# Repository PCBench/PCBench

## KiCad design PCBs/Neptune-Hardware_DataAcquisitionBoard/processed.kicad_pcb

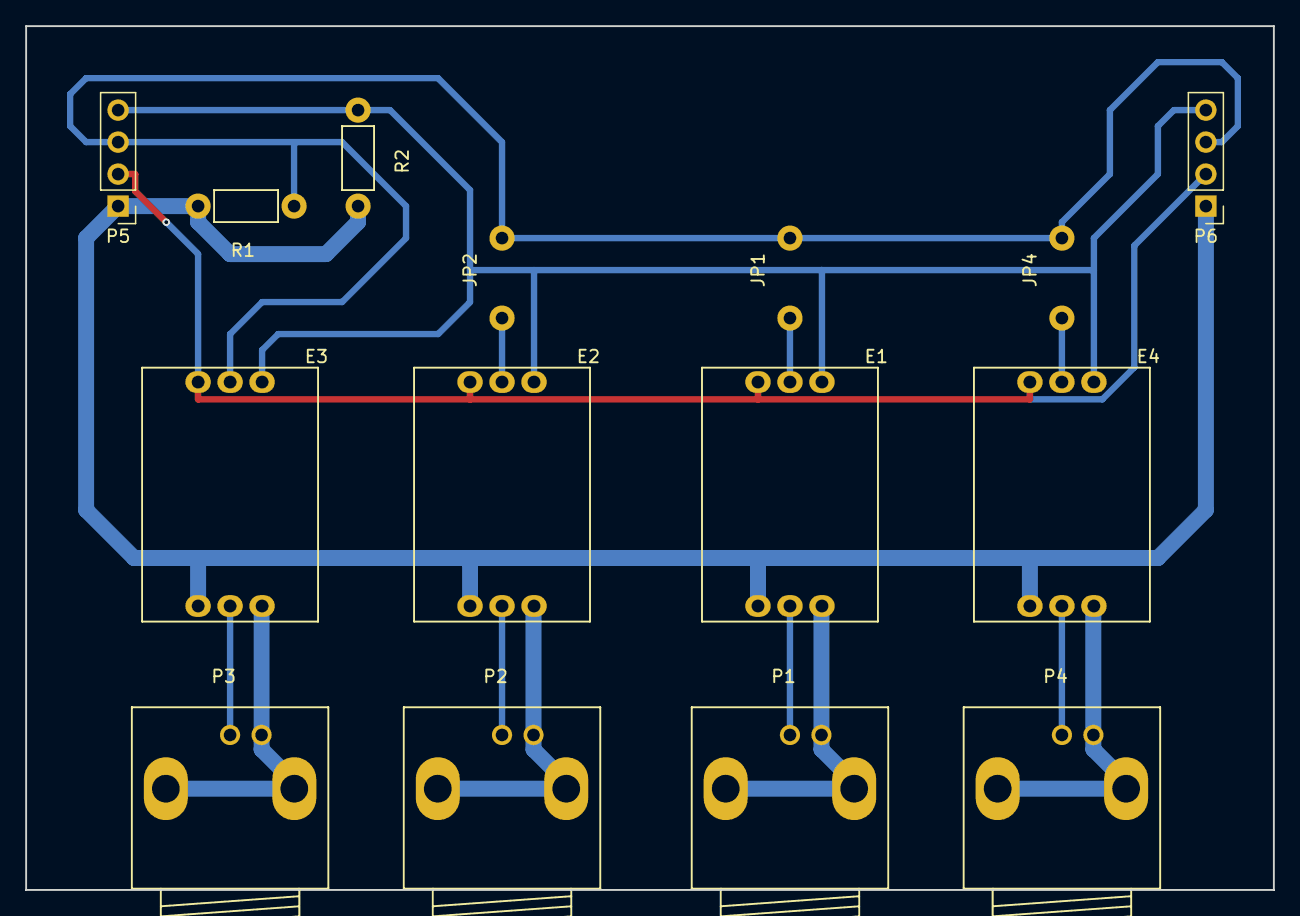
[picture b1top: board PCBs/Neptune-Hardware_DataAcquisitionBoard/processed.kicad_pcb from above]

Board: 2 copper layers, 99.1 x 68.6 mm, 15 parts (0 on the bottom side), 15 nets.

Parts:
E1, E3, E4: phEZO
E2: DO_EZO; phEZO
JP1, JP2, JP4: JUMPER; Jumper_6.35mm
P1, P2, P3, P4: BNC; BNC_Socket_TYCO-AMP
P5, P6: CONN_01X04; Pin_Header_Straight_1x04_Pitch2.54mm
R1, R2: 12K; Resistor_Horizontal_RM7mm

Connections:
+5V: E1.6, E2.6, E3.6, E4.6, P5.1, P6.1, R1.2, R2.2
A4: E3.2, JP1.2, JP2.2, JP4.2, P5.3, P6.3, R1.1
A5: E1.3, E2.3, E3.3, E4.3, P5.4, P6.4, R2.1
GND: E1.1, E2.1, E3.1, E4.1, P5.2, P6.2
unnamed: E1.2, JP1.1
unnamed: E1.4, P1.2
unnamed: E1.5, P1.1
unnamed: E2.2, JP2.1
unnamed: E2.4, P2.2
unnamed: E2.5, P2.1
unnamed: E3.4, P3.2
unnamed: E3.5, P3.1
unnamed: E4.2, JP4.1
unnamed: E4.4, P4.2
unnamed: E4.5, P4.1

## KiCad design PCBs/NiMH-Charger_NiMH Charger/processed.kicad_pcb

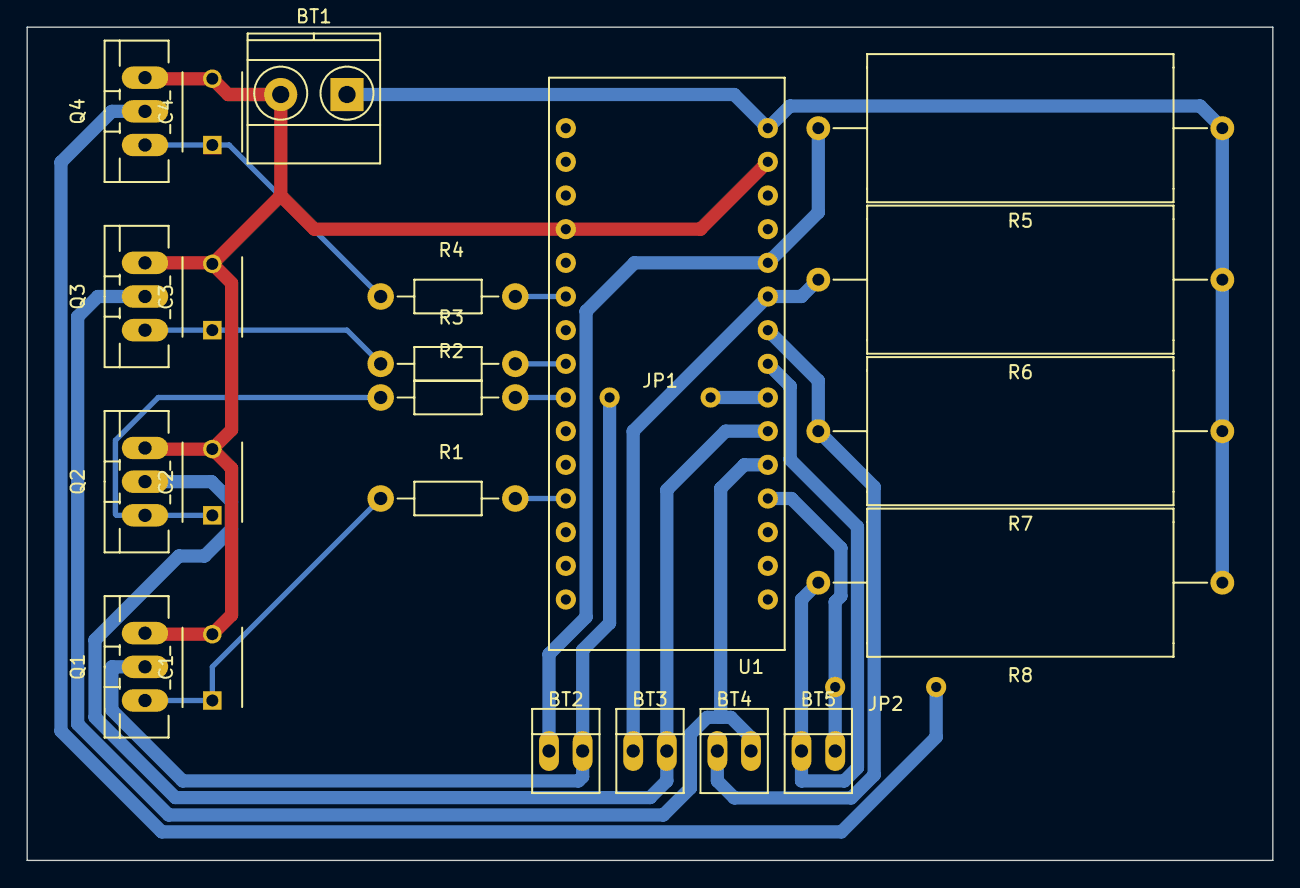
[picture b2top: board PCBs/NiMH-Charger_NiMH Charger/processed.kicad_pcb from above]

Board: 2 copper layers, 94.0 x 62.9 mm, 24 parts (0 on the bottom side), 20 nets.

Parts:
BT1: Battery; TerminalBlock_Pheonix_MKDS1.5-2pol
BT2, BT3, BT4, BT5: Battery; PINHEAD1-2
C1, C2, C3, C4: 1uF; C_Disc_D6_P5
JP1, JP2: JUMPER; Jumper
Q1, Q2, Q3, Q4: IRF510; TO-220_Neutral123_Vertical_LargePads
R1, R2, R3, R4: 10M; Resistor_Horizontal_RM10mm
R5, R6, R7, R8: 10R; Resistor_Ceramic_Horizontal_L23mm-W9mm-H9mm-p30mm
U1: Arduino_NANO

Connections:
/GND: BT1.2, C1.2, C2.2, C3.2, C4.2, Q1.3, Q2.3, Q3.3, Q4.3, U1.14, U1.19
/VIN: BT1.1, R5.1, R6.1, R7.1, R8.1, U1.15
unnamed: BT2.1, R5.2, U1.11
unnamed: BT2.2, JP1.2, Q1.2
unnamed: BT3.1, R6.2, U1.10
unnamed: BT3.2, Q2.2, U1.6
unnamed: BT4.1, R7.2, U1.9
unnamed: BT4.2, Q3.2, U1.5
unnamed: BT5.1, R8.2, U1.8
unnamed: BT5.2, JP2.1, U1.4
unnamed: C1.1, Q1.1, R1.1
unnamed: C2.1, Q2.1, R2.1
unnamed: C3.1, Q3.1, R3.1
unnamed: C4.1, Q4.1, R4.1
unnamed: JP1.1, U1.7
unnamed: JP2.2, Q4.2
unnamed: R1.2, U1.27
unnamed: R2.2, U1.24
unnamed: R3.2, U1.23
unnamed: R4.2, U1.21

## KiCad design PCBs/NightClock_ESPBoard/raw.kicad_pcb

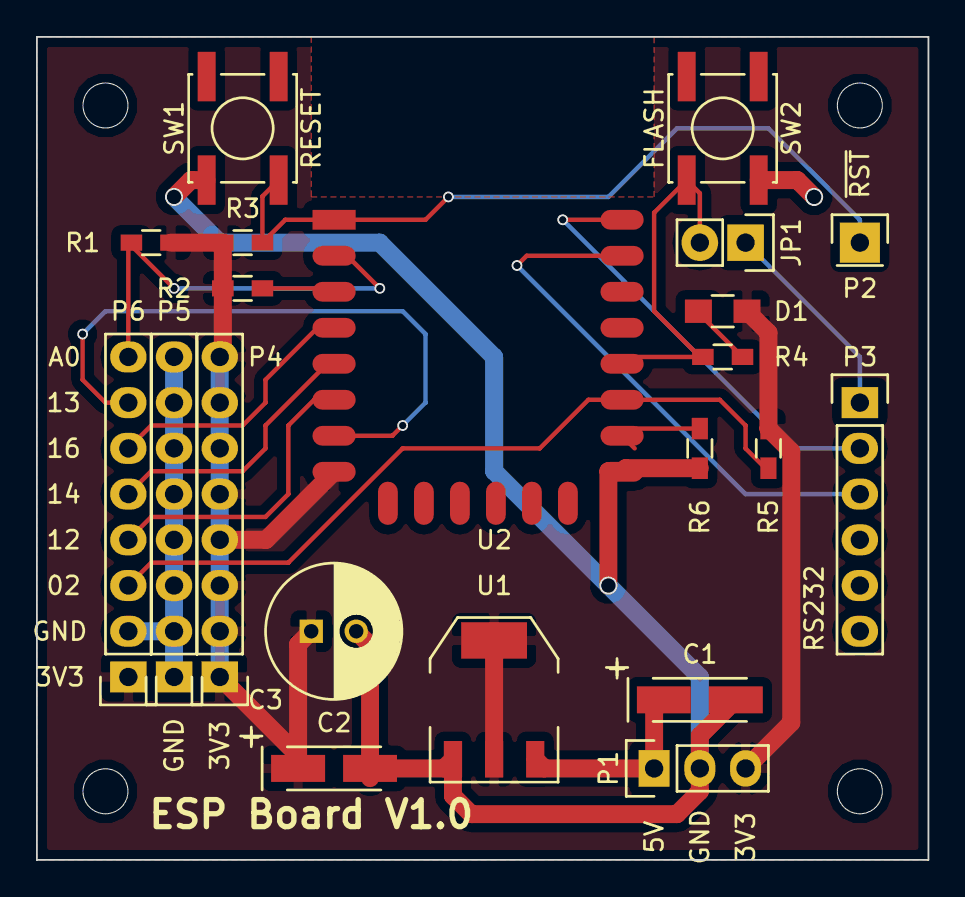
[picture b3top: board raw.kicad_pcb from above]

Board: 2 copper layers, 49.5 x 45.7 mm, 21 parts (0 on the bottom side), 17 nets.

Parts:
C1, C2: 10u; TantalC_SizeA_EIA-3216_HandSoldering
C3: 1000u; C_Radial_D7.5_L11.2_P2.5
D1: LED; R_0805_HandSoldering
JP1: AUTO_FLASH; Pin_Header_Straight_1x02
P1: PWR; Pin_Header_Straight_1x03
P2: EXT_RESET; Pin_Header_Straight_1x01
P3: RS232; Pin_Header_Straight_1x06
P4: 3.3V; Pin_Header_Straight_1x08
P5: Gnd; Pin_Header_Straight_1x08
P6: GPIO; Pin_Header_Straight_1x08
R1: 470k; R_0603_HandSoldering
R2, R3, R5, R6: 10k; R_0603_HandSoldering
R4: 330R; R_0603_HandSoldering
SW1: RESET; SW_SPST_EVPBF
SW2: FLASH; SW_SPST_EVPBF
U1: LM1117-3.3; SOT-223
U2: ESP-12E

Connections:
+3V3: C2.1, C3.1, D1.2, P1.3, P4.1, P4.2, P4.3, P4.4, P4.5, P4.6, P4.7, P4.8, P6.1, R1.1, R2.1, R3.1, R5.1, U1.2, U1.4, U2.8
+5V: C1.1, P1.1, U1.3
/ESP_ADC: P6.8, R1.2, U2.2
/ESP_CH_PD: R2.2, U2.3
/ESP_GPIO0: JP1.2, R4.2, SW2.2, U2.18
/ESP_GPIO2: P6.3, R5.2, U2.17
/ESP_GPIO12: P6.4, U2.6
/ESP_GPIO13: P6.7, U2.7
/ESP_GPIO14: P6.5, U2.5
/ESP_GPIO15: R6.1, U2.16
/ESP_GPIO16: P6.6, U2.4
/ESP_RESET: P2.1, R3.2, SW1.2, U2.1
/ESP_RX_IN: P3.3, U2.21
/ESP_TX_OUT: P3.2, U2.22
/SERIAL_DTR: JP1.1, P3.1
GNDPWR: C1.2, C2.2, C3.2, P1.2, P3.6, P5.1, P5.2, P5.3, P5.4, P5.5, P5.6, P5.7, P5.8, P6.2, R6.2, SW1.1, SW2.1, U1.1, U2.15
unnamed: D1.1, R4.1

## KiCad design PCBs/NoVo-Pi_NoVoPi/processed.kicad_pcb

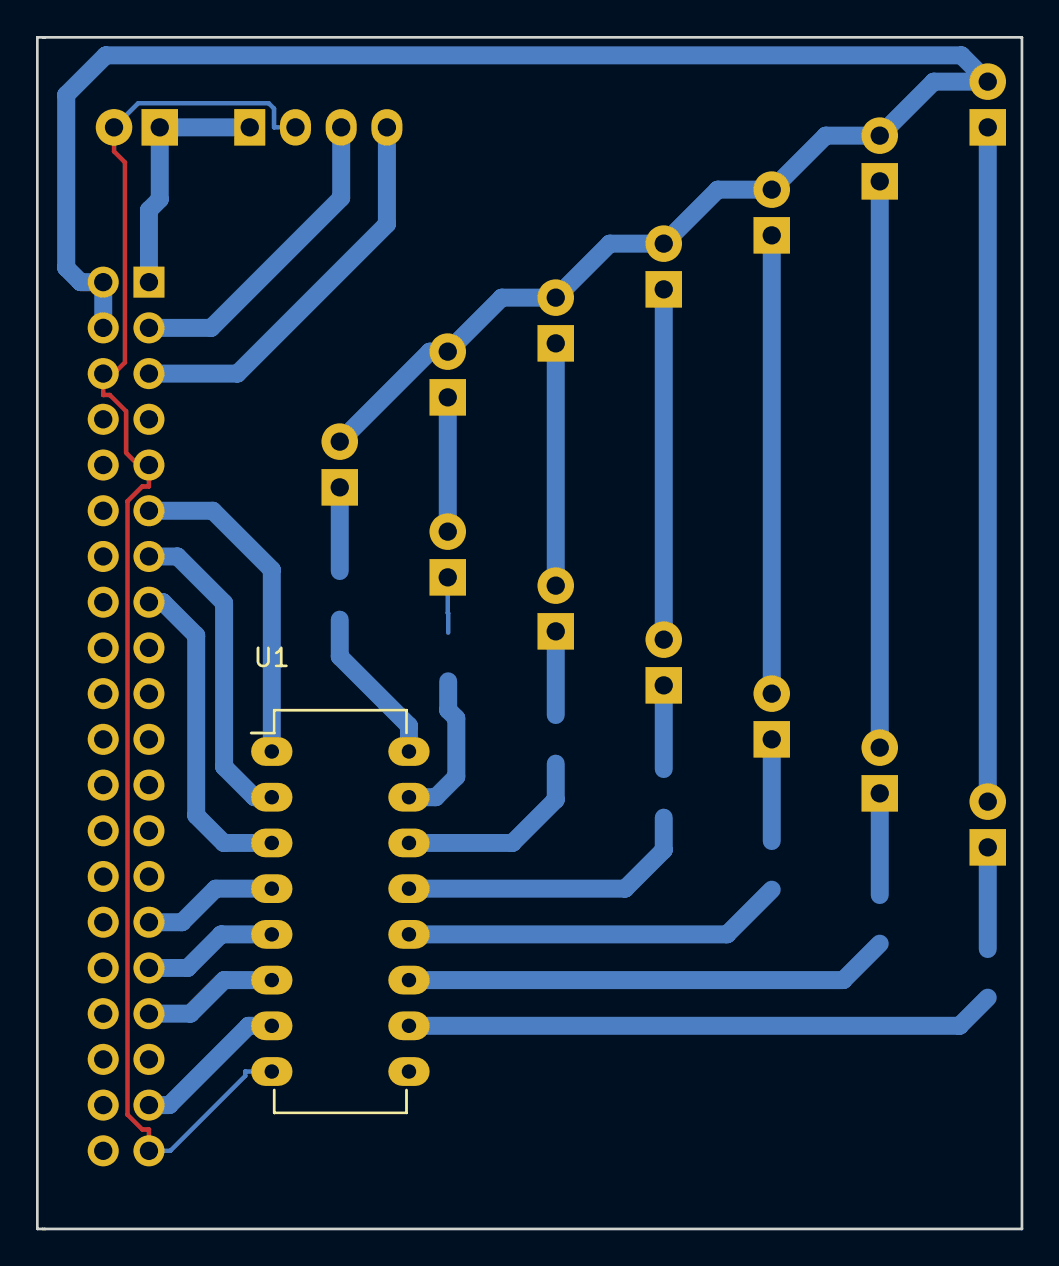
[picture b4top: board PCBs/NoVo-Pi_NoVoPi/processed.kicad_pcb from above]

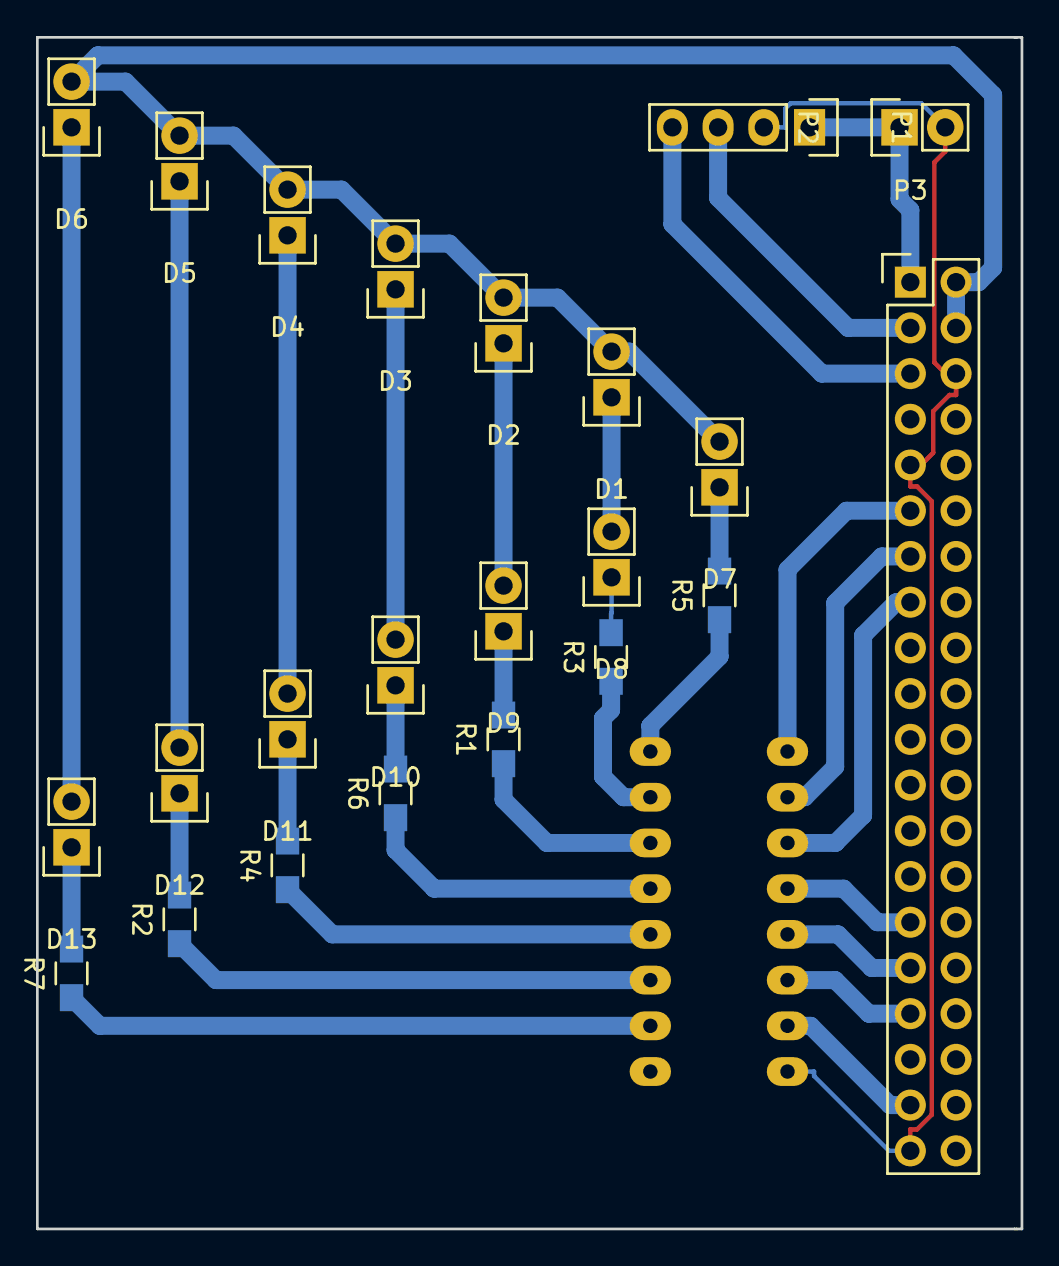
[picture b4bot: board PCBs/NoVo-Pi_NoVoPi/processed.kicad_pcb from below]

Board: 2 copper layers, 54.7 x 66.2 mm, 24 parts (23 on the bottom side), 32 nets.

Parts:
D1, D2, D3, D4, D5, D6, D7, D8, D9, D10, D11, D12, D13: LED; Pin_Header_Straight_1x02
P1: CONN_01X04; Pin_Header_Straight_1x04
P2: CONN_01X02; Pin_Header_Straight_1x02
P3: CONN_02X20; Pin_Header_Straight_2x20
R1, R2, R3, R4, R6, R7: 100; R_0805_HandSoldering
R5: 220; R_0805_HandSoldering
U1: ULN2003A; DIP-16_W7.62mm_LongPads

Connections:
+3V3: P1.1, P2.1, P3.1
+5V: D1.2, D2.2, D3.2, D4.2, D5.2, D6.2, D7.2, P3.2, P3.4
GND: P1.2, P2.2, P3.6, P3.9, P3.39, U1.8
unnamed: D1.1, D8.2
unnamed: D2.1, D9.2
unnamed: D7.1, R5.2
unnamed: D8.1, R3.2
unnamed: D9.1, R1.2
unnamed: D10.1, R6.2
unnamed: D3.1, D10.2
unnamed: D11.1, R4.2
unnamed: D4.1, D11.2
unnamed: D12.1, R2.2
unnamed: D5.1, D12.2
unnamed: D13.1, R7.2
unnamed: D6.1, D13.2
unnamed: P1.3, P3.3
unnamed: P1.4, P3.5
unnamed: P3.11, U1.1
unnamed: P3.13, U1.2
unnamed: P3.15, U1.3
unnamed: P3.29, U1.4
unnamed: P3.31, U1.5
unnamed: P3.33, U1.6
unnamed: P3.37, U1.7
unnamed: R1.1, U1.14
unnamed: R2.1, U1.11
unnamed: R3.1, U1.15
unnamed: R4.1, U1.12
unnamed: R5.1, U1.16
unnamed: R6.1, U1.13
unnamed: R7.1, U1.10

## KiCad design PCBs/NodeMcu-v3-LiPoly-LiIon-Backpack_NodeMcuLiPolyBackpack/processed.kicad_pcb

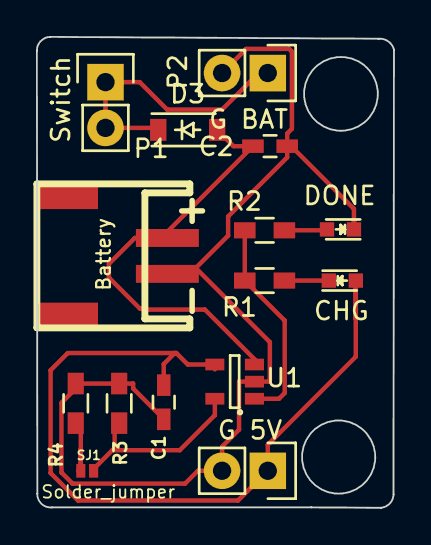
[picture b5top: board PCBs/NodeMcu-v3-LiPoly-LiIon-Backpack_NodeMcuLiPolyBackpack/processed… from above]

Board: 2 copper layers, 19.8 x 26.2 mm, 16 parts (1 on the bottom side), 9 nets.

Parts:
C1, C2: 10uF; C_0603_HandSoldering
D1: CHG; LED-0603
D2: DONE; LED-0603
D3: MBR120; SOD-123
LOGO: LOGO
P1: Switch; Pin_Header_Straight_1x02
P2: G BAT; Pin_Header_Straight_1x02
P3: Battery; CONN_JST-2_SMD
P4: G 5V; Pin_Header_Straight_1x02
R1, R2: 1K; R_0603_HandSoldering
R3: 10K; R_0603_HandSoldering
R4: 2.5K; R_0603_HandSoldering
SJ1: Solder_jumper; S_JUMPER_2
U1: MCP73831; SOT-23-5

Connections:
/VBUS: C1.1, D1.2, P4.1, U1.4
/VBat: C2.1, D3.2, P3.1, U1.3
GND: C1.2, C2.2, D2.1, P2.2, P3.2, P4.2, R3.1, R4.1, U1.2
unnamed: D1.1, R1.2
unnamed: D2.2, R2.2
unnamed: D3.1, P1.1, P1.2, P2.1
unnamed: R1.1, R2.1, U1.1
unnamed: R3.2, SJ1.1, U1.5
unnamed: R4.2, SJ1.2

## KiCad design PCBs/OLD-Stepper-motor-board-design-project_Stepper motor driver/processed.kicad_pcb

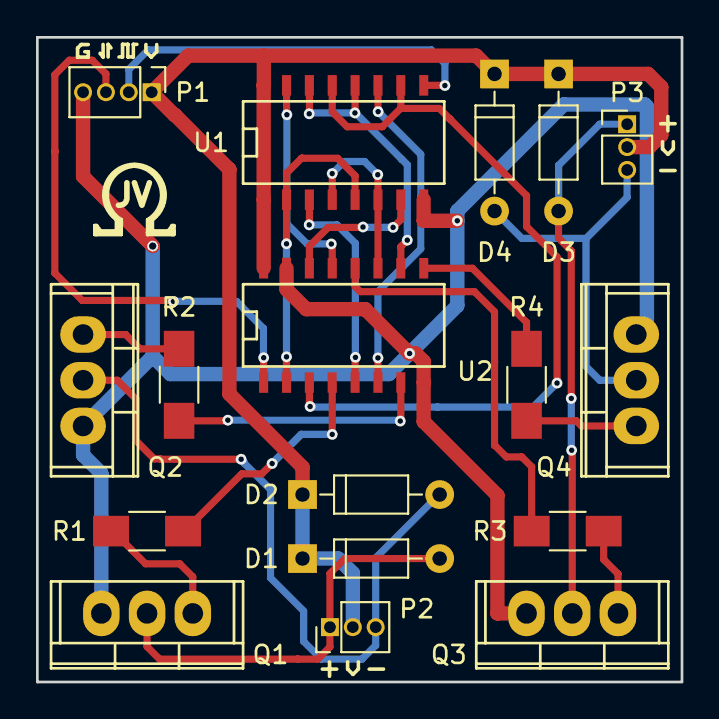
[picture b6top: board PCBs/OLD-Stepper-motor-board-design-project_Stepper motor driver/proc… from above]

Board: 2 copper layers, 35.8 x 35.8 mm, 17 parts (0 on the bottom side), 24 nets.

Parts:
D1, D2, D3, D4: 1N4003; D_DO-35_SOD27_P7.62mm_Horizontal
P1: CONN_01X04; Pin_Header_Straight_1x04_Pitch1.27mm
P2, P3: CONN_01X03; Pin_Header_Straight_1x03_Pitch1.27mm
Q1, Q2, Q3, Q4: TIP120; TO-220
R1, R2, R3, R4: 180; R_1206_HandSoldering
U1: 74LS175; SO-16-N
U2: 74LS157; SO-16-N

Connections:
/A1+: U1.4, U1.6, U2.11
/A1-: U1.7, U2.14
/A2+: U1.11, U2.6
/A2-: U1.10, U1.13, U2.3
/B1+: U1.2, U1.5, U2.2
/B1-: U1.3, U2.5
/B2+: U1.15, U2.13
/B2-: U1.12, U1.14, U2.10
/CLK: P1.2, U1.9
/Coil1+: D1.2, P2.1, Q1.2
/Coil1-: D2.2, P2.3, Q2.2
/Coil2+: D3.2, P3.1, Q3.2
/Coil2-: D4.2, P3.3, Q4.2
/DIR: P1.3, U2.1
GND: P1.4, Q1.3, Q2.3, Q3.3, Q4.3, U1.8, U2.8, U2.15
unnamed: Q1.1, R1.1
unnamed: Q2.1, R2.1
unnamed: Q3.1, R3.1
unnamed: Q4.1, R4.1
unnamed: R1.2, U2.4
unnamed: R2.2, U2.7
unnamed: R3.2, U2.12
unnamed: R4.2, U2.9
VCC: D1.1, D2.1, D3.1, D4.1, P1.1, P2.2, P3.2, U1.1, U1.16, U2.16
